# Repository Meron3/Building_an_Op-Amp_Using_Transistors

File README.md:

# トランジスタで作るスピーカーアンプ

トランジスタ16石で作るスピーカーアンプのkicadプロジェクトです。

kicad9.0以降で開くことができます。

トグルスイッチのフットプリントは、nosuz様のkicad-libをインポートして使用しています。
https://github.com/nosuz/kicad-lib

# 回路図

# Overview

# Building an Op-Amp Using Transistors

This is a KiCad project for a speaker amplifier using 16 transistors.

It can be opened with KiCad 9.0 or later.

The toggle switch footprint uses KiCad-lib imported by nosuz.
https://github.com/nosuz/kicad-lib

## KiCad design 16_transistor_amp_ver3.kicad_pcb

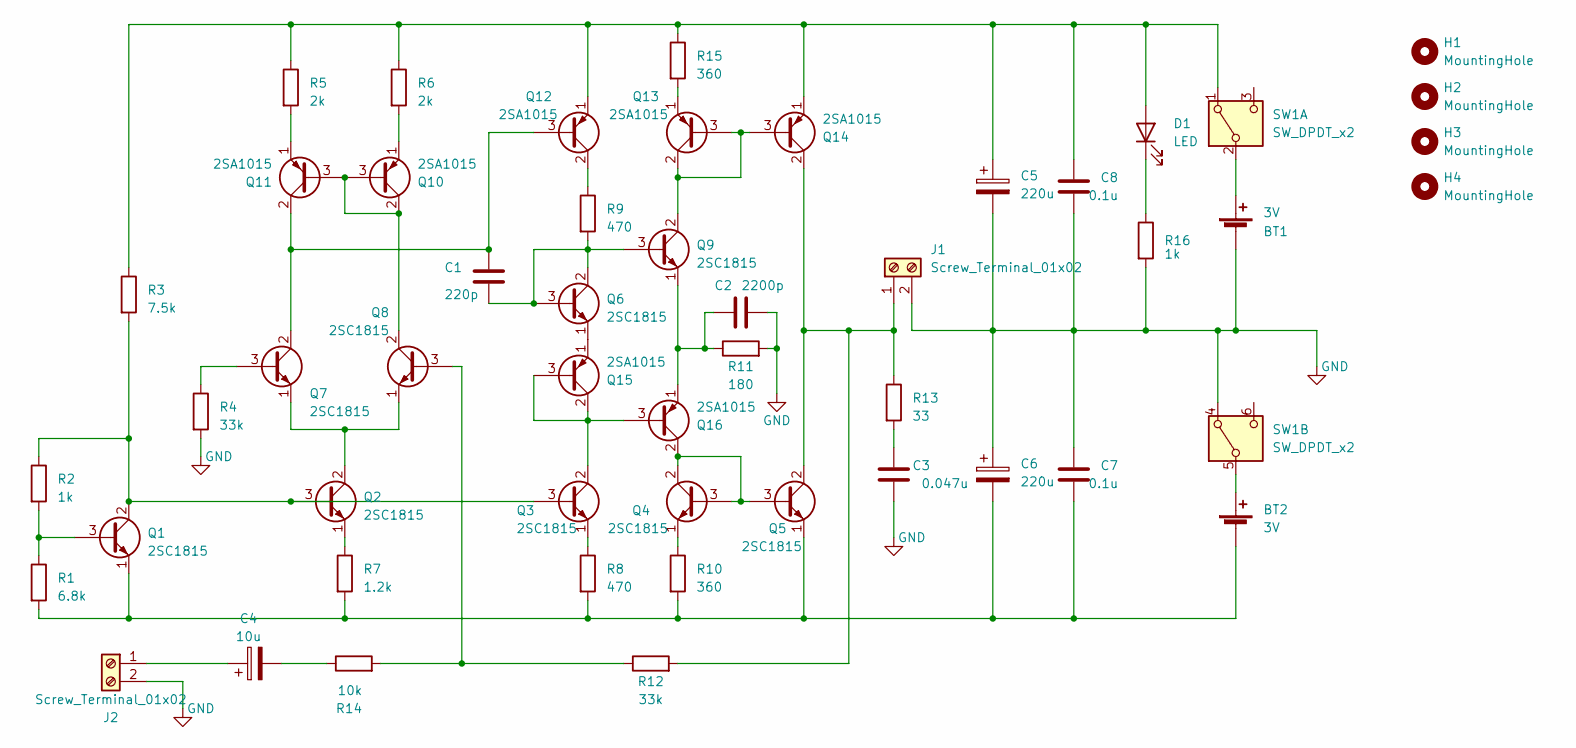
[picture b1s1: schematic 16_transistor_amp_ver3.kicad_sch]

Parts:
BT1, BT2: 3V; PinHeader_1x02_P2.54mm_Vertical
C1: 220p; C_Disc_D4.7mm_W2.5mm_P5.00mm
C2: 2200p; C_Disc_D4.7mm_W2.5mm_P5.00mm
C3: 0.047u; C_Disc_D4.7mm_W2.5mm_P5.00mm
C4: 10u; CP_Radial_D8.0mm_P3.50mm
C5, C6: 220u; CP_Radial_D6.3mm_P2.50mm
C7, C8: 0.1u; C_Disc_D3.0mm_W1.6mm_P2.50mm
D1: LED; LED_D3.0mm
H1, H2, H3, H4: MountingHole; MountingHole_3.2mm_M3
J1, J2: Screw_Terminal_01x02; TerminalBlock_bornier-2_P5.08mm
Q1, Q2, Q3, Q4, Q5, Q6, Q7, Q8, Q9: 2SC1815; TO-92_Inline_Wide
Q10, Q11, Q12, Q13, Q14, Q15, Q16: 2SA1015; TO-92_Inline_Wide
R1: 6.8k; R_Axial_DIN0207_L6.3mm_D2.5mm_P10.16mm_Horizontal
R2, R16: 1k; R_Axial_DIN0207_L6.3mm_D2.5mm_P10.16mm_Horizontal
R3: 7.5k; R_Axial_DIN0207_L6.3mm_D2.5mm_P10.16mm_Horizontal
R4, R12: 33k; R_Axial_DIN0207_L6.3mm_D2.5mm_P10.16mm_Horizontal
R5, R6: 2k; R_Axial_DIN0207_L6.3mm_D2.5mm_P10.16mm_Horizontal
R7: 1.2k; R_Axial_DIN0207_L6.3mm_D2.5mm_P10.16mm_Horizontal
R8, R9: 470; R_Axial_DIN0207_L6.3mm_D2.5mm_P10.16mm_Horizontal
R10, R15: 360; R_Axial_DIN0207_L6.3mm_D2.5mm_P10.16mm_Horizontal
R11: 180; R_Axial_DIN0207_L6.3mm_D2.5mm_P10.16mm_Horizontal
R13: 33; R_Axial_DIN0207_L6.3mm_D2.5mm_P10.16mm_Horizontal
R14: 10k; R_Axial_DIN0207_L6.3mm_D2.5mm_P10.16mm_Horizontal
SW1: SW_DPDT_x2; 2MD1-T2-B4-M2-Q-N

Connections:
GND: BT1.2 (-), C2.1, C3.2, C5.2, C6.1, C7.2, C8.1, J1.2, J2.2, R4.2, R11.2, R16.2, SW1.4 (A)
unnamed: BT1.1 (+), SW1.2 (B)
unnamed: BT2.1 (+), SW1.5 (B)
unnamed: BT2.2 (-), C6.2, C7.1, Q1.1 (E), Q5.1 (E), R1.2, R7.2, R8.2, R10.2
unnamed: C3.1, R13.2
unnamed: C4.2, R14.1
unnamed: C5.1, C8.2, D1.2 (A), Q12.1 (E), Q14.1 (E), R3.1, R5.1, R6.1, R15.1, SW1.1 (A)
unnamed: D1.1 (K), R16.1
unnamed: J1.1, Q5.2 (C), Q14.2 (C), R12.2, R13.1
unnamed: C4.1, J2.1
unnamed: Q1.3 (B), R1.1, R2.2
unnamed: Q1.2 (C), Q2.3 (B), Q3.3 (B), R2.1, R3.2
unnamed: Q2.2 (C), Q7.1 (E), Q8.1 (E)
unnamed: Q2.1 (E), R7.1
unnamed: Q3.1 (E), R8.1
unnamed: Q4.1 (E), R10.1
unnamed: C1.2, Q6.2 (C), Q6.3 (B), Q9.3 (B), R9.2
unnamed: Q7.3 (B), R4.1
unnamed: Q8.3 (B), R12.1, R14.2
unnamed: Q8.2 (C), Q10.2 (C), Q10.3 (B), Q11.3 (B)
unnamed: Q10.1 (E), R6.2
unnamed: C1.1, Q7.2 (C), Q11.2 (C), Q12.3 (B)
unnamed: Q11.1 (E), R5.2
unnamed: Q12.2 (C), R9.1
unnamed: Q9.2 (C), Q13.2 (C), Q13.3 (B), Q14.3 (B)
unnamed: Q13.1 (E), R15.2
unnamed: Q3.2 (C), Q15.2 (C), Q15.3 (B), Q16.3 (B)
unnamed: Q6.1 (E), Q15.1 (E)
unnamed: Q4.2 (C), Q4.3 (B), Q5.3 (B), Q16.2 (C)
unnamed: C2.2, Q9.1 (E), Q16.1 (E), R11.1

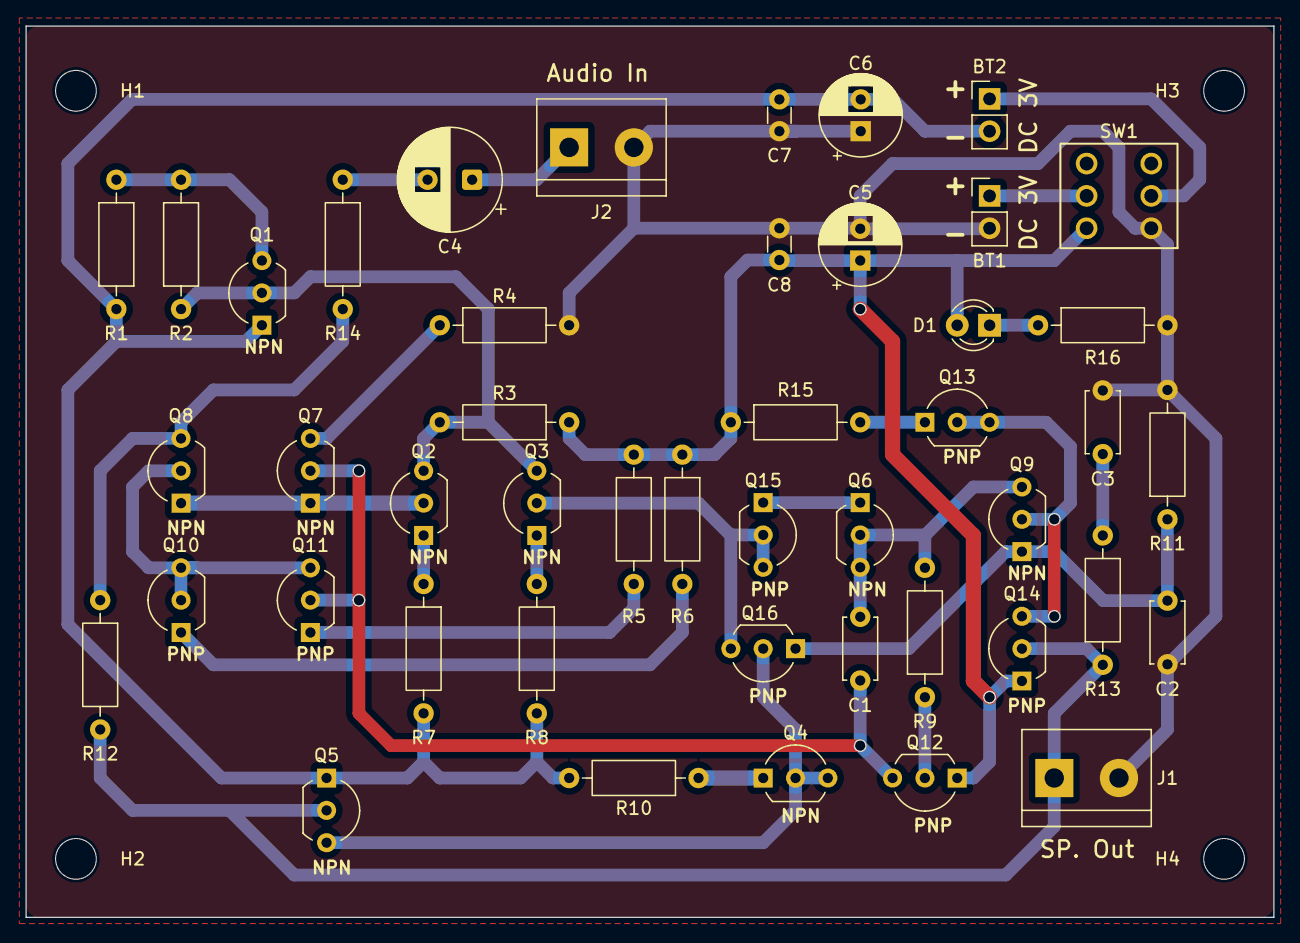
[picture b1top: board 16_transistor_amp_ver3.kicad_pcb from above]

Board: 2 copper layers, 98.0 x 70.0 mm, 50 parts (0 on the bottom side), 30 nets.

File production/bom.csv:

Designator,Footprint,Quantity,Value,LCSC Part #
"BT1, BT2",PinHeader_1x02_P2.54mm_Vertical,2,3V,
C1,C_Disc_D4.7mm_W2.5mm_P5.00mm,1,220p,
C2,C_Disc_D4.7mm_W2.5mm_P5.00mm,1,2200p,
C3,C_Disc_D4.7mm_W2.5mm_P5.00mm,1,0.047u,
C4,CP_Radial_D8.0mm_P3.50mm,1,10u,
"C5, C6",CP_Radial_D6.3mm_P2.50mm,2,220u,
"C7, C8",C_Disc_D3.0mm_W1.6mm_P2.50mm,2,0.1u,
D1,LED_D3.0mm,1,LED,
"J1, J2",TerminalBlock_bornier-2_P5.08mm,2,Screw_Terminal_01x02,
"Q1, Q2, Q3, Q4, Q5, Q6, Q7, Q8, Q9",TO-92_Inline_Wide,9,2SC1815,
"Q10, Q11, Q12, Q13, Q14, Q15, Q16",TO-92_Inline_Wide,7,2SA1015,
R1,R_Axial_DIN0207_L6.3mm_D2.5mm_P10.16mm_Horizontal,1,6.8k,
"R10, R15",R_Axial_DIN0207_L6.3mm_D2.5mm_P10.16mm_Horizontal,2,360,
R11,R_Axial_DIN0207_L6.3mm_D2.5mm_P10.16mm_Horizontal,1,180,
"R12, R4",R_Axial_DIN0207_L6.3mm_D2.5mm_P10.16mm_Horizontal,2,33k,
R13,R_Axial_DIN0207_L6.3mm_D2.5mm_P10.16mm_Horizontal,1,33,
R14,R_Axial_DIN0207_L6.3mm_D2.5mm_P10.16mm_Horizontal,1,10k,
"R16, R2",R_Axial_DIN0207_L6.3mm_D2.5mm_P10.16mm_Horizontal,2,1k,
R3,R_Axial_DIN0207_L6.3mm_D2.5mm_P10.16mm_Horizontal,1,7.5k,
"R5, R6",R_Axial_DIN0207_L6.3mm_D2.5mm_P10.16mm_Horizontal,2,2k,
R7,R_Axial_DIN0207_L6.3mm_D2.5mm_P10.16mm_Horizontal,1,1.2k,
"R8, R9",R_Axial_DIN0207_L6.3mm_D2.5mm_P10.16mm_Horizontal,2,470,
SW1,2MD1-T2-B4-M2-Q-N,1,SW_DPDT_x2,
